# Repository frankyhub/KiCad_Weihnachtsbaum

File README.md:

# KiCad_Weihnachtsbaum
Platine, NANO, LEDs und Jingle Bells Melodie

<div align="center">

|[:skull:ISSUE](https://github.com/frankyhub/KiCad_Weihnachtsbaum/issues?q=is%3Aissue)|[:speech_balloon: Forum /Discussion](https://github.com/frankyhub/KiCad_Weihnachtsbaum/discussions)|[:grey_question:WiKi](https://github.com/frankyhub/KiCad_Weihnachtsbaum/wiki)||
|--|--|--|--|
| | | | |
||<a href="https://github.com/frankyhub/KiCad_Weihnachtsbaum/issues">|<a href="https://github.com/frankyhub/KiCad_Weihnachtsbaum/discussions">|<a href="https://github.com/frankyhub/KiCad_Weihnachtsbaum/releases">|
|| <a href="https://github.com/frankyhub/KiCad_Weihnachtsbaum/pulse" alt="Activity">| <a href="https://github.com/frankyhub/KiCad_Weihnachtsbaum/graphs/traffic">  |<a href="https://github.com/frankyhub?tab=stars"> |
</div>

## BOM

| Anzahl | Bezeichnung | 
| -------- | -------- | 
| 1  |  NANO Shield	  |
| 1  |  NANO |
|  1 |  Buzzer|  
| 9  |  R1	100  |
|  9 |  LED 5mm| 
|  1 | Batterieclip 9V	   |
| 1  | 9V Batterie   |
| -------- | -------- | 

---

<div style="position:absolute; left:2cm; ">   
<ol class="breadcrumb" style="border-top: 2px solid black;border-bottom:2px solid black; height: 45px; width: 900px;"> <p align="center"><a href="#oben">nach oben</a></p></ol>
</div>  

---

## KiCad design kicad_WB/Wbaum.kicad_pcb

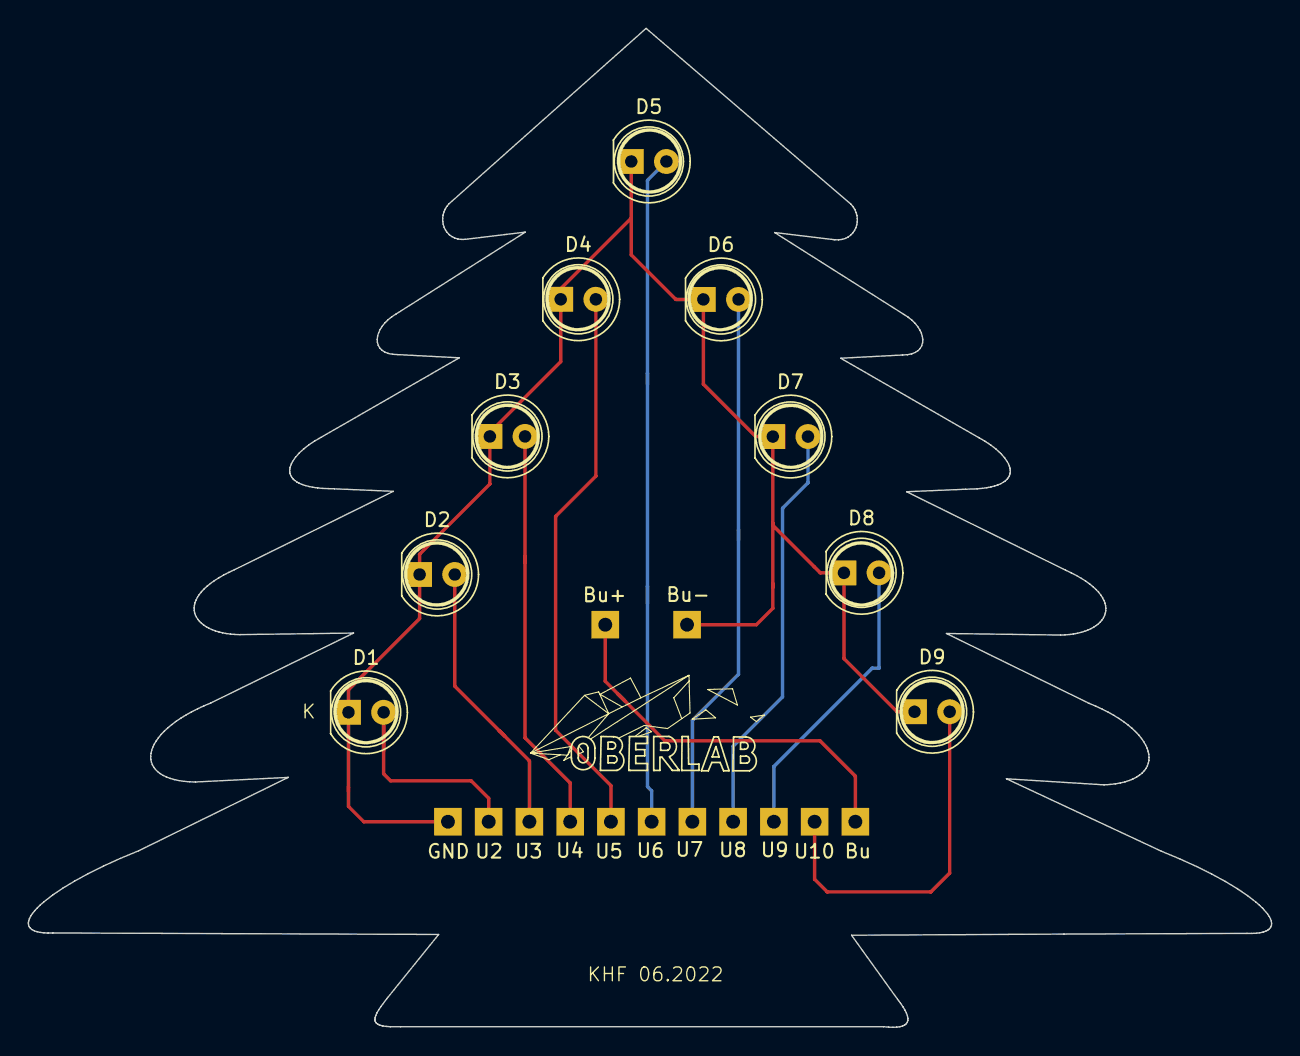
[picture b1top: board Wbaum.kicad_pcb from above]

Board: 2 copper layers, 89.9 x 72.2 mm, 22 parts (0 on the bottom side), 11 nets.

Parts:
Bu: LP
Bu+: LP
Bu-: LP_GND; LP
D1, D2, D3, D4, D5, D6, D7, D8, D9: LED; LED_D5.0mm
GND: LP
U2, U3, U4, U5, U6, U7, U8, U9, U10: LP

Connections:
unnamed: Bu-.1, D1.1, D2.1, D3.1, D4.1, D5.1, D6.1, D7.1, D8.1, D9.1, GND.1
unnamed: D1.2, U2.1
unnamed: D2.2, U3.1
unnamed: D3.2, U4.1
unnamed: D4.2, U5.1
unnamed: D5.2, U6.1
unnamed: D6.2, U7.1
unnamed: D7.2, U8.1
unnamed: D8.2, U9.1
unnamed: D9.2, U10.1
unnamed: Bu.1, Bu+.1

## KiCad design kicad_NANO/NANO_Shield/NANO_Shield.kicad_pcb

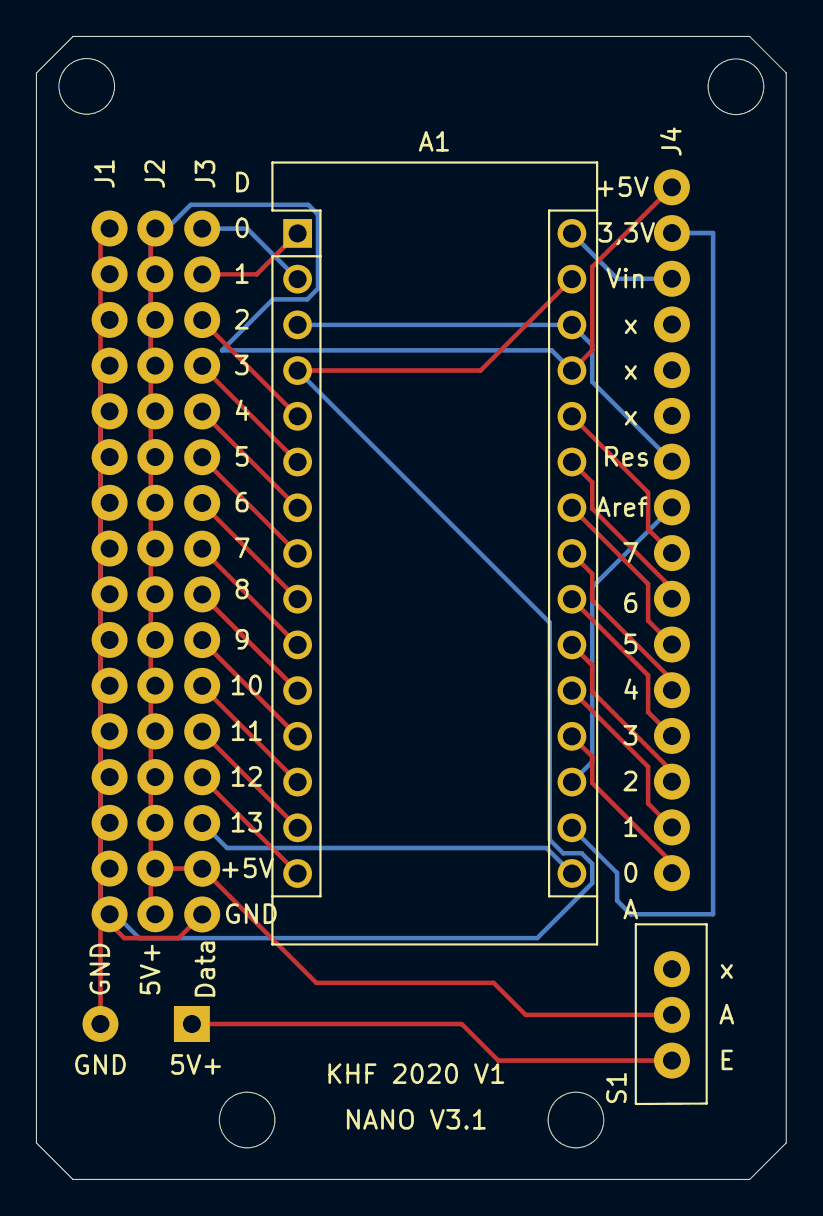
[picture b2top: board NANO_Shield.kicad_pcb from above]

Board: 2 copper layers, 41.7 x 63.5 mm, 7 parts (0 on the bottom side), 29 nets.

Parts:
A1: Arduino_Nano_v3.x; Arduino_Nano
GND: 9VBat; 9VBAT_khf
J1, J2, J3, J4: NANO16PINStiftleiste; NANO_Stift_16PIN
S1: Micro_Schalter; Micro_SchalterKHF

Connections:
unnamed: A1.1, J3.2
unnamed: A1.2, J3.1
unnamed: A1.5, J3.3
unnamed: A1.6, J3.4
unnamed: A1.7, J3.5
unnamed: A1.8, J3.6
unnamed: A1.9, J3.7
unnamed: A1.10, J3.8
unnamed: A1.11, J3.9
unnamed: A1.12, J3.10
unnamed: A1.13, J3.11
unnamed: A1.14, J3.12
unnamed: A1.15, J3.13
unnamed: A1.16, J3.14
unnamed: A1.17, J4.15
unnamed: A1.18, J4.9
unnamed: A1.19, J4.1
unnamed: A1.20, J4.2
unnamed: A1.21, J4.3
unnamed: A1.22, J4.4
unnamed: A1.23, J4.5
unnamed: A1.24, J4.6
unnamed: A1.25, J4.7
unnamed: A1.26, J4.8
unnamed: A1.27, J2.1, J2.2, J2.3, J2.4, J2.5, J2.6, J2.7, J2.8, J2.9, J2.10, J2.11, J2.12, J2.13, J2.14, J2.15, J2.16, J3.15, J4.16, S1.2
unnamed: A1.3, A1.28, J4.10
unnamed: A1.4, A1.29, GND.1, J1.1, J1.2, J1.3, J1.4, J1.5, J1.6, J1.7, J1.8, J1.9, J1.10, J1.11, J1.12, J1.13, J1.14, J1.15, J1.16, J3.16
unnamed: A1.30, J4.14
unnamed: GND.2, S1.1

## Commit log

2025-12-02 V02122025
2025-12-02 V01122025
    Added badges, images, and BOM details to README.
